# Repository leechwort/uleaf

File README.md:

# uLEAF

**uLEAF** is a minimalistic STM32 platform for developing audio synthesis applications. It was primarily designed for use with [LEAF (Lightweight Embedded Audio Framework)](https://github.com/spiricom/LEAF), but is not limited to it. 

### Hardware Features
* **Powerful MCU:** Cortex-M33 (STM32H533) with memory-mapped 8 MB PSRAM
* **Storage:** 8 MB additional external Flash memory
* **Audio:** Audio DAC PCM5102A

### Design Philosophy
This development board tries to be as cheap and simple as possible. It is designed to be highly versatile, allowing you to easily embed it directly into your own projects or use it as a starting point to develop your own custom PCB based on this design.

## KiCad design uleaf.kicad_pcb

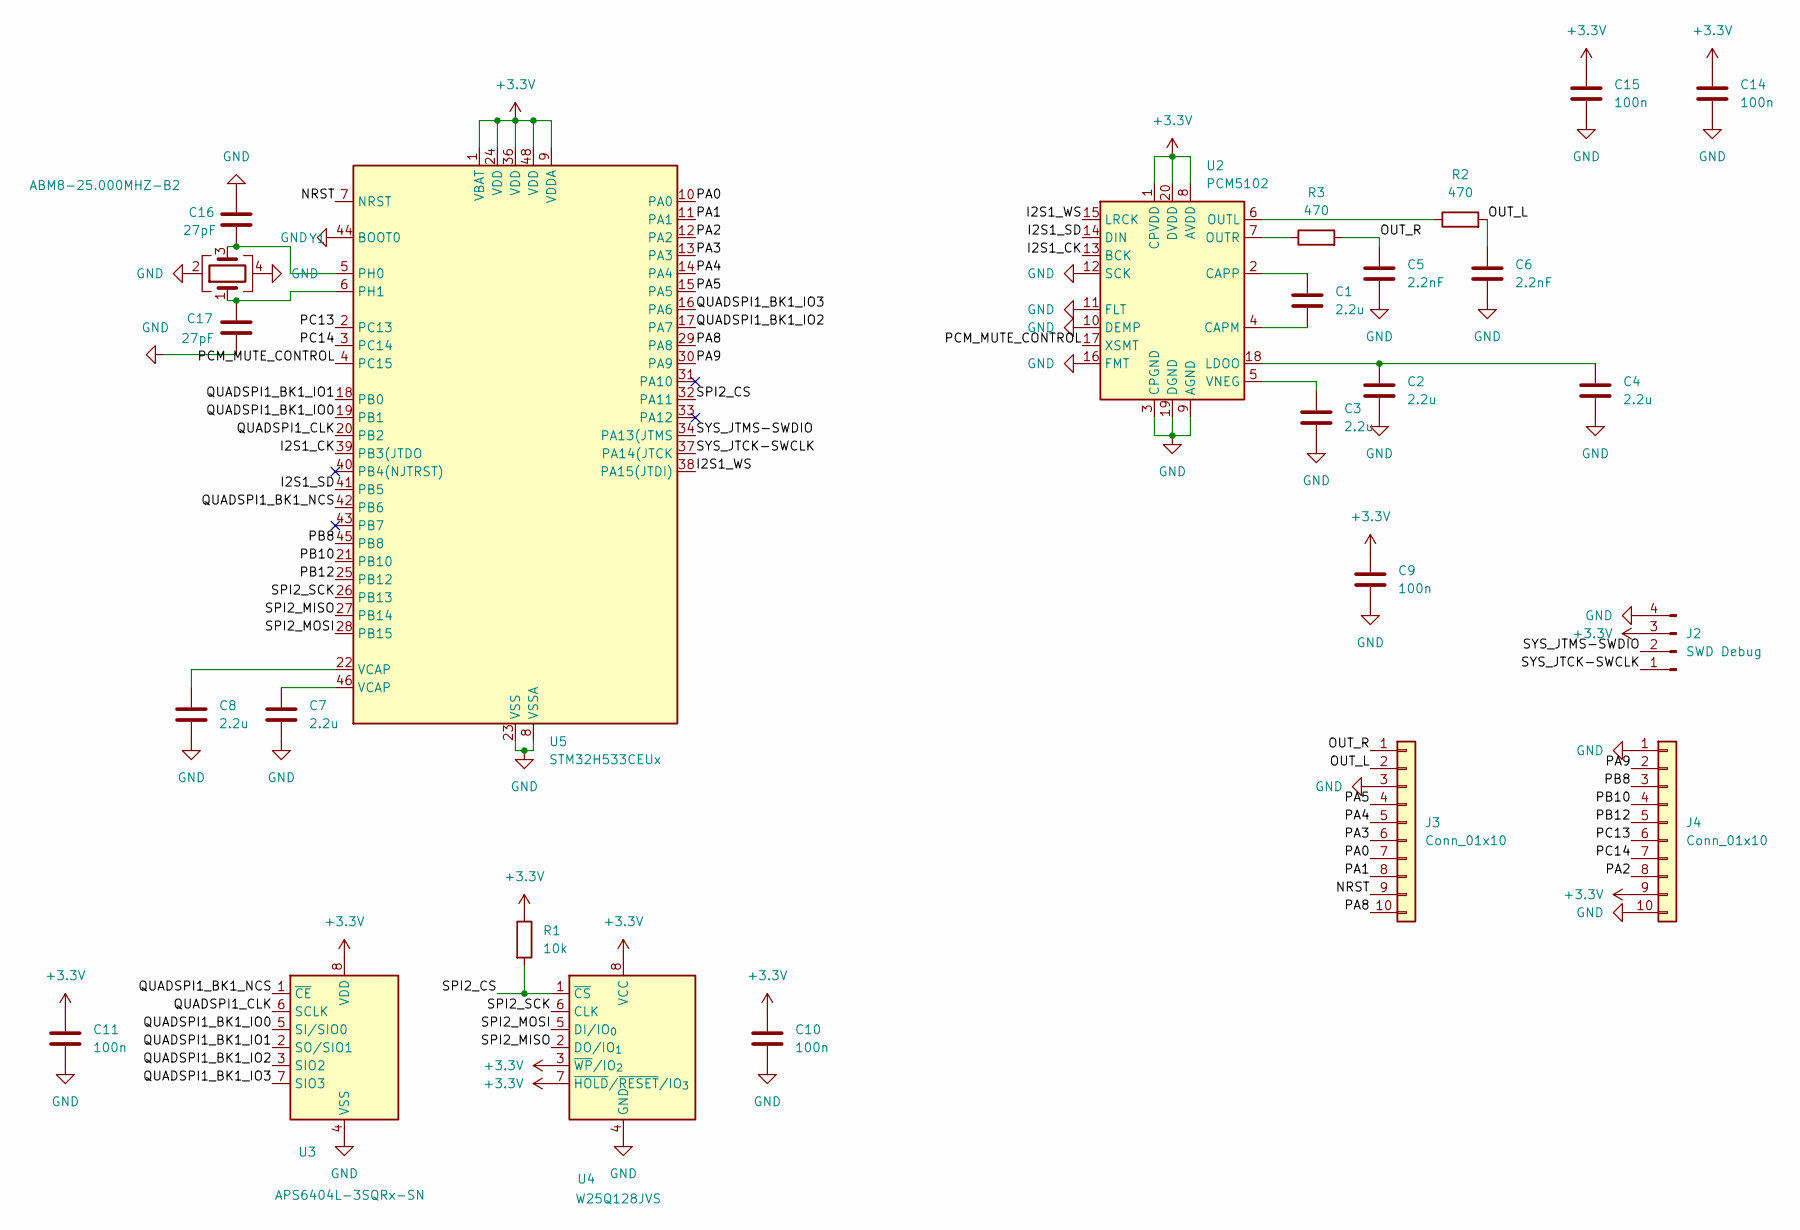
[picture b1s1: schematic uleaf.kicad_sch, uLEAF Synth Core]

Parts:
C1, C2, C3, C4, C7, C8: 2.2u; C_0603_1608Metric
C5, C6: 2.2nF; C_0603_1608Metric
C9, C10, C11, C14, C15: 100n; C_0603_1608Metric
C16, C17: 27pF; C_0603_1608Metric
J2: SWD Debug; PinHeader_1x04_P2.54mm_Vertical
J3, J4: Conn_01x10; PinHeader_1x10_P2.54mm_Vertical_Castellated
R1: 10k; R_0603_1608Metric
R2, R3: 470; R_0603_1608Metric
U2: PCM5102; TSSOP-20_4.4x6.5mm_P0.65mm
U3: APS6404L-3SQRx-SN; SOIC-8_3.9x4.9mm_P1.27mm
U4: W25Q128JVS; SOIC-8_5.3x5.3mm_P1.27mm
U5: STM32H533CEUx; QFN-48-1EP_7x7mm_P0.5mm_EP5.6x5.6mm
Y1: ABM8-25.000MHZ-B2; Crystal_SMD_3225-4Pin_3.2x2.5mm

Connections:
+3.3V: C9.2, C10.2, C11.2, C14.2, C15.2, J2.3, J4.9, R1.1, U2.1 (CPVDD), U2.8 (AVDD), U2.20 (DVDD), U3.8 (VDD), U4.3 (~WP/IO_{2}), U4.7 (~HOLD/~RESET/IO_{3}), U4.8 (VCC), U5.1 (VBAT), U5.9 (VDDA), U5.24 (VDD), U5.36 (VDD), U5.48 (VDD)
/I2S1_CK: U2.13 (BCK), U5.39 (PB3(JTDO)
/I2S1_SD: U2.14 (DIN), U5.41 (PB5)
/I2S1_WS: U2.15 (LRCK), U5.38 (PA15(JTDI))
/NRST: J3.9, U5.7 (NRST)
/OUT_L: C6.2, J3.2, R2.2
/OUT_R: C5.2, J3.1, R3.2
/PA0: J3.7, U5.10 (PA0)
/PA1: J3.8, U5.11 (PA1)
/PA2: J4.8, U5.12 (PA2)
/PA3: J3.6, U5.13 (PA3)
/PA4: J3.5, U5.14 (PA4)
/PA5: J3.4, U5.15 (PA5)
/PA8: J3.10, U5.29 (PA8)
/PA9: J4.2, U5.30 (PA9)
/PB8: J4.3, U5.45 (PB8)
/PB10: J4.4, U5.21 (PB10)
/PB12: J4.5, U5.25 (PB12)
/PC13: J4.6, U5.2 (PC13)
/PC14: J4.7, U5.3 (PC14)
/PCM_MUTE_CONTROL: U2.17 (XSMT), U5.4 (PC15)
/QUADSPI1_BK1_IO0: U3.5 (SI/SIO0), U5.19 (PB1)
/QUADSPI1_BK1_IO1: U3.2 (SO/SIO1), U5.18 (PB0)
/QUADSPI1_BK1_IO2: U3.3 (SIO2), U5.17 (PA7)
/QUADSPI1_BK1_IO3: U3.7 (SIO3), U5.16 (PA6)
/QUADSPI1_BK1_NCS: U3.1 (~CE), U5.42 (PB6)
/QUADSPI1_CLK: U3.6 (SCLK), U5.20 (PB2)
/SPI2_CS: R1.2, U4.1 (~CS), U5.32 (PA11)
/SPI2_MISO: U4.2 (DO/IO_{1}), U5.27 (PB14)
/SPI2_MOSI: U4.5 (DI/IO_{0}), U5.28 (PB15)
/SPI2_SCK: U4.6 (CLK), U5.26 (PB13)
/SYS_JTCK-SWCLK: J2.1, U5.37 (PA14(JTCK)
/SYS_JTMS-SWDIO: J2.2, U5.34 (PA13(JTMS)
GND: C2.1, C3.1, C4.1, C5.1, C6.1, C7.1, C8.1, C9.1, C10.1, C11.1, C14.1, C15.1, C16.2, C17.1, J2.4, J3.3, J4.1, J4.10, U2.3 (CPGND), U2.9 (AGND), U2.10 (DEMP), U2.11 (FLT), U2.12 (SCK), U2.16 (FMT), U2.19 (DGND), U3.4 (VSS), U4.4 (GND), U5.8 (VSSA), U5.23 (VSS), U5.35 (VSS), U5.44 (BOOT0), U5.47 (VSS), U5.49 (VSS), Y1.2, Y1.4
unnamed: C7.2, U5.46 (VCAP)
unnamed: C8.2, U5.22 (VCAP)
unnamed: C1.1, U2.4 (CAPM)
unnamed: C1.2, U2.2 (CAPP)
unnamed: C2.2, C4.2, U2.18 (LDOO)
unnamed: R2.1, U2.6 (OUTL)
unnamed: R3.1, U2.7 (OUTR)
unnamed: C3.2, U2.5 (VNEG)
unnamed: C16.1, U5.5 (PH0), Y1.3
unnamed: C17.2, U5.6 (PH1), Y1.1

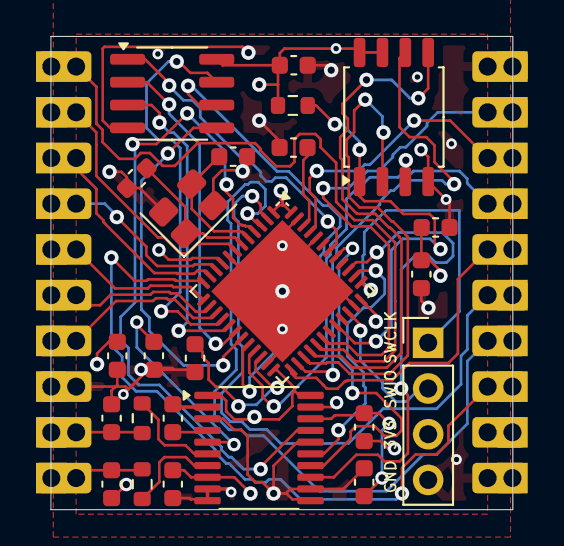
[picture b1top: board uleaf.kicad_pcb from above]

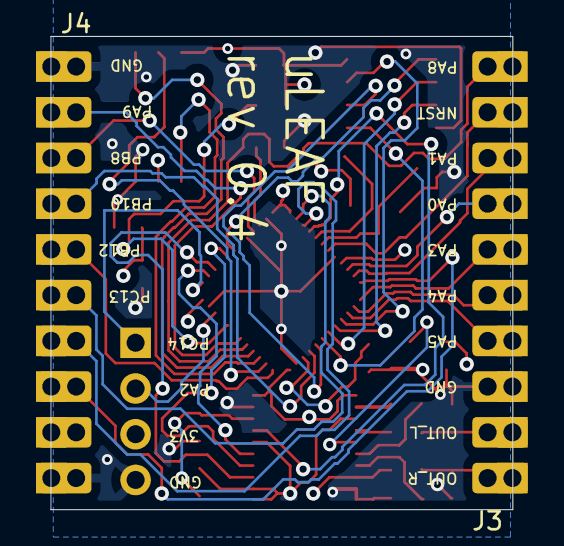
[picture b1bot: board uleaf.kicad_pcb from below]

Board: 4 copper layers, 25.7 x 26.3 mm, 26 parts (2 on the bottom side), 44 nets.

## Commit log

2025-11-27 Initial plan
2025-11-27 Add comprehensive README with uLEAF project description
2025-11-27 Added project files
2025-11-27 Add uleaf.png image to README.md
2026-02-14 Fixed problem with VNEG pin
2026-02-22 Fixed problem with output DAC output filters
2026-02-22 Added 3d model
2026-02-22 Readme update
2026-03-07 Added values for crystal and caps
2026-05-10 Fixed problems with pcm connections, rev 0.4
